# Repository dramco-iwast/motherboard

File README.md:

# motherboard
Design files (soft- and hardware) for the IWAST motherboard.

Needs reorganization.

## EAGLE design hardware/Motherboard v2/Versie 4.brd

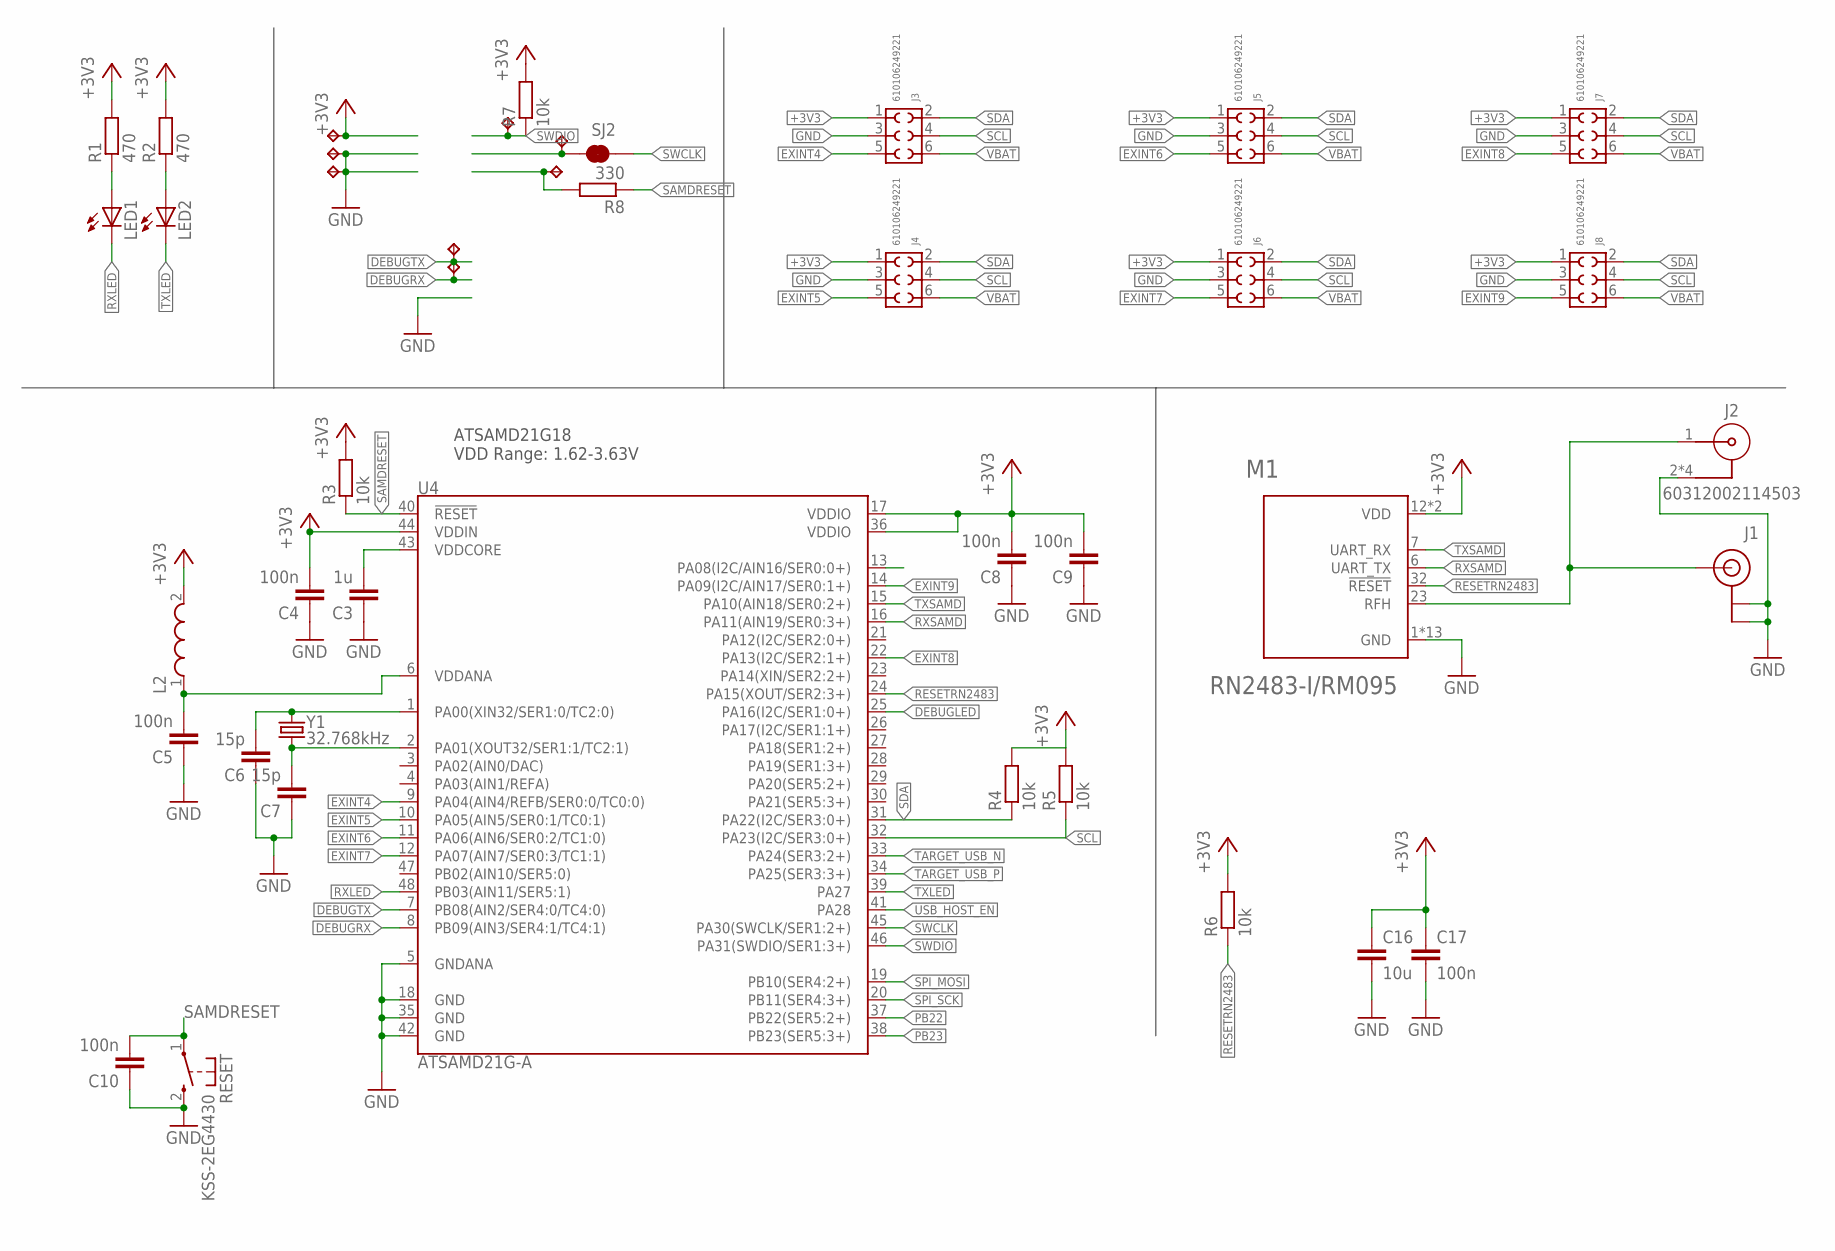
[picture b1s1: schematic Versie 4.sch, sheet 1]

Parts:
C3: 1u; C0603
C4, C5, C8, C9, C10, C17: 100n; C0603
C6, C7: 15p; C0603
C16: 10u; C0805
J1: U.FL
J2: 60312002114503
J3, J4, J5, J6, J7, J8: 610106249221
L2: WE-CBA_0603(WB/HS); WE-CBA_0603(W=2.2)
LED1, LED2: LEDCHIP-LED0603; CHIP-LED0603
M1: RN2483-I/RM095; MICROCHIP_RN2483-I/RM095
R1, R2: 470; R0603
R3, R4, R5, R6, R7: 10k; R0603
R8: 330; R0603
RESET: KSS-2EG4430
SJ2: JUMPER-PAD-2-NC_BY_TRACENO_SILK; PAD-JUMPER-2-NC_BY_TRACE_NO_SILK
TP1, TP2, TP3, TP4, TP5, TP6, TP7, TP8: TPB1,27; B1,27
U4: ATSAMD21G-A; TQFP-48
Y1: 32.768kHz; CRYSTAL-SMD-3.2X1.5MM

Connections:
+3V3: C4.2, C8.2, C9.2, C16.1, C17.1, J3.1, J4.1, J5.1, J6.1, J7.1, J8.1, L2.2, M1.12 (VDD), M1.34 (VDD), R1.2, R2.2, R3.2, R4.2, R5.2, R6.2, R7.2, TP1.TP, U4.17 (VDDIO), U4.36 (VDDIO), U4.44 (VDDIN); also elsewhere on the board
BUTTON: U4.13 (PA08(I2C/AIN16/SER0:0+)); also elsewhere on the board
DEBUGLED: U4.25 (PA16(I2C/SER1:0+)); also elsewhere on the board
DEBUGRX: TP8.TP, U4.8 (PB09(AIN3/SER4:1/TC4:1))
DEBUGTX: TP7.TP, U4.7 (PB08(AIN2/SER4:0/TC4:0))
EXINT4: J3.5, U4.9 (PA04(AIN4/REFB/SER0:0/TC0:0))
EXINT5: J4.5, U4.10 (PA05(AIN5/SER0:1/TC0:1))
EXINT6: J5.5, U4.11 (PA06(AIN6/SER0:2/TC1:0))
EXINT7: J6.5, U4.12 (PA07(AIN7/SER0:3/TC1:1))
EXINT8: J7.5, U4.22 (PA13(I2C/SER2:1+))
EXINT9: J8.5, U4.14 (PA09(I2C/AIN17/SER0:1+))
GND: C3.1, C4.1, C5.1, C6.1, C7.1, C8.1, C9.1, C10.1, C16.2, C17.2, J1.P$1 (GND), J1.P$2 (GND), J2.2, J2.3 (2), J2.4 (2), J2.5 (2), J3.3, J4.3, J5.3, J6.3, J7.3, J8.3, M1.1 (GND), M1.8 (GND), M1.11 (GND), M1.20 (GND), M1.21 (GND), M1.22 (GND), M1.24 (GND), M1.26 (GND), M1.27 (GND), M1.28 (GND), M1.33 (GND), M1.41 (GND), M1.47 (GND), RESET.2 (S), TP2.TP, TP3.TP, U4.5 (GNDANA), U4.18 (GND), U4.35 (GND), U4.42 (GND); also elsewhere on the board
unnamed: LED1.A, R1.1
unnamed: LED2.A, R2.1
unnamed: SJ2.2, TP5.TP
unnamed: C6.2, U4.1 (PA00(XIN32/SER1:0/TC2:0)), Y1.P$2 (2)
unnamed: C7.2, U4.2 (PA01(XOUT32/SER1:1/TC2:1)), Y1.P$1 (1)
unnamed: C5.2, L2.1, U4.6 (VDDANA)
unnamed: J1.P$3 (SIGNAL), J2.1, M1.23 (RFH)
unnamed: R8.2, TP6.TP
PB22: U4.37 (PB22(SER5:2+))
PB23: U4.38 (PB23(SER5:3+))
RESETRN2483: M1.32 (!RESET), R6.1, U4.24 (PA15(XOUT/SER2:3+))
RXLED: LED1.C, U4.48 (PB03(AIN11/SER5:1))
RXSAMD: M1.6 (UART_TX), U4.16 (PA11(AIN19/SER0:3+))
SAMDRESET: C10.2, R3.1, R8.1, RESET.1, U4.40 (!RESET!); also elsewhere on the board
SCL: J3.4, J4.4, J5.4, J6.4, J7.4, J8.4, R5.1, U4.32 (PA23(I2C/SER3:0+))
SDA: J3.2, J4.2, J5.2, J6.2, J7.2, J8.2, R4.1, U4.31 (PA22(I2C/SER3:0+))
SPI_MOSI: U4.19 (PB10(SER4:2+))
SPI_SCK: U4.20 (PB11(SER4:3+))
SWCLK: SJ2.1, U4.45 (PA30(SWCLK/SER1:2+))
SWDIO: R7.1, TP4.TP, U4.46 (PA31(SWDIO/SER1:3+))
TARGET_USB_N: U4.33 (PA24(SER3:2+)); also elsewhere on the board
TARGET_USB_P: U4.34 (PA25(SER3:3+)); also elsewhere on the board
TXLED: LED2.C, U4.39 (PA27)
TXSAMD: M1.7 (UART_RX), U4.15 (PA10(AIN18/SER0:2+))
USB_HOST_EN: U4.41 (PA28)
VBAT: J3.6, J4.6, J5.6, J6.6, J7.6, J8.6; also elsewhere on the board
VDDCORE: C3.2, U4.43 (VDDCORE)

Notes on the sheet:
ATSAMD21G18 VDD Range: 1.62-3.63V

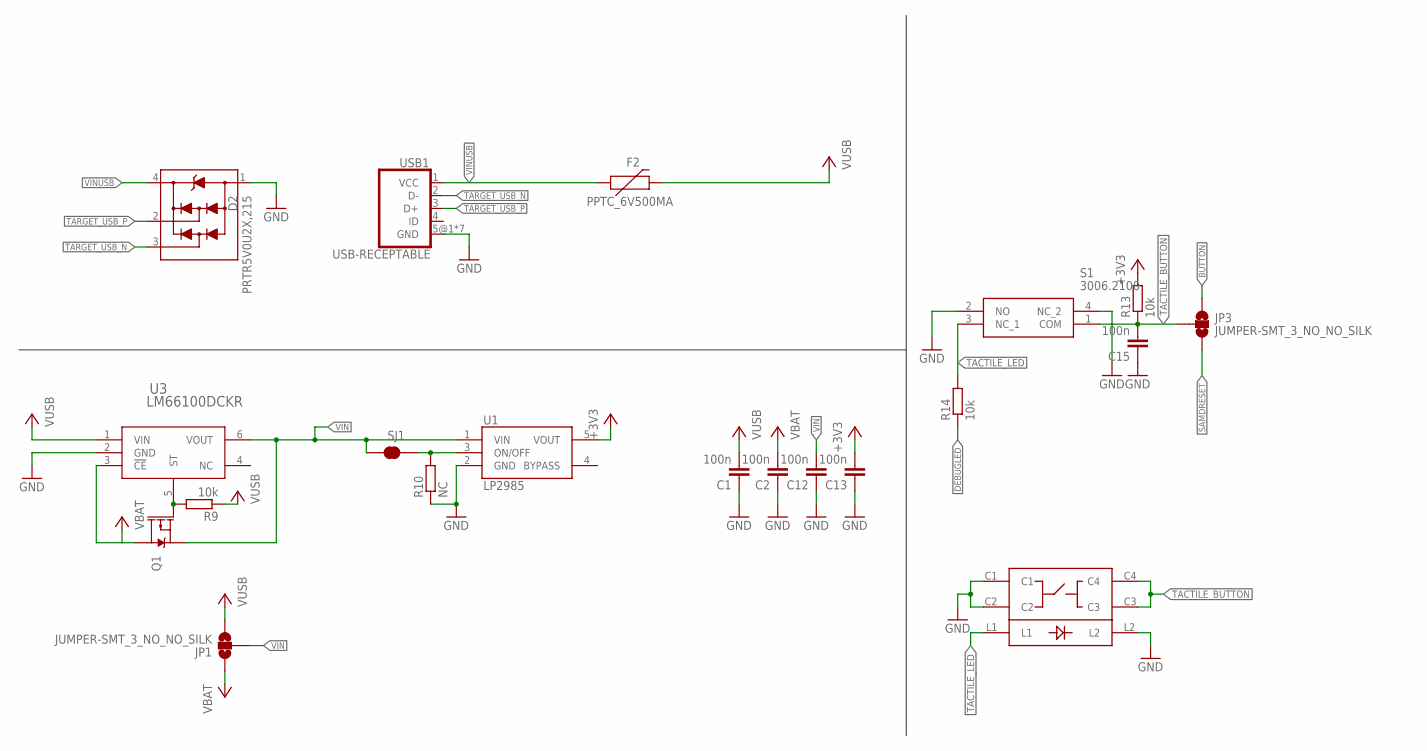
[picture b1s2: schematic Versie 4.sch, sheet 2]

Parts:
C1, C2, C12, C13, C15: 100n; C0603
D2: PRTR5V0U2X,215; SOT143B
F2: PPTC_6V500MA; 0805
JP1, JP3: JUMPER-SMT_3_NO_NO_SILK; SMT-JUMPER_3_0-NO_TRACE_NO-SILK
Q1: MOSFET_PCH-DMG2307L; SOT23-3
R9, R13, R14: 10k; R0603
R10: NC; R0603
S1: 3006.2100; 30062101
SJ1: JUMPER-PAD-2-NC_BY_TRACENO_SILK; PAD-JUMPER-2-NC_BY_TRACE_NO_SILK
U1: LP2985AIM5-3.3; SOT25
U3: LM66100DCKR; DCK6_TEX
U$1: LS1201
USB1: USB-RECEPTABLE; FCI-10103594-0001LF

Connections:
+3V3: C13.2, R13.2, U1.5 (VOUT); also elsewhere on the board
BUTTON: JP3.1; also elsewhere on the board
DEBUGLED: R14.1; also elsewhere on the board
GND: C1.1, C2.1, C12.1, C13.1, C15.1, D2.1, R10.1, S1.2 (NO), S1.4 (NC_2), U1.2 (GND), U3.2 (GND), U$1.C1, U$1.C2, U$1.L2, USB1.5@1 (GND), USB1.5@2 (GND), USB1.5@3 (GND), USB1.5@4 (GND), USB1.5@5 (GND), USB1.5@6 (GND), USB1.5@7 (GND); also elsewhere on the board
unnamed: Q1.1 (G), R9.2, U3.5 (ST)
ONOFF: R10.2, SJ1.1, U1.3 (ON/OFF)
SAMDRESET: JP3.3; also elsewhere on the board
TACTILE_BUTTON: C15.2, JP3.2, R13.1, S1.1 (COM), U$1.C3, U$1.C4
TACTILE_LED: R14.2, S1.3 (NC_1), U$1.L1
TARGET_USB_N: D2.3, USB1.2 (D-); also elsewhere on the board
TARGET_USB_P: D2.2, USB1.3 (D+); also elsewhere on the board
VBAT: C2.2, JP1.1, Q1.3 (D), U3.3 (!CE); also elsewhere on the board
VIN: C12.2, JP1.2, Q1.2 (S), SJ1.2, U1.1 (VIN), U3.6 (VOUT)
VINUSB: D2.4, F2.1, USB1.1 (VCC)
VUSB: C1.2, F2.2, JP1.3, R9.1, U3.1 (VIN)

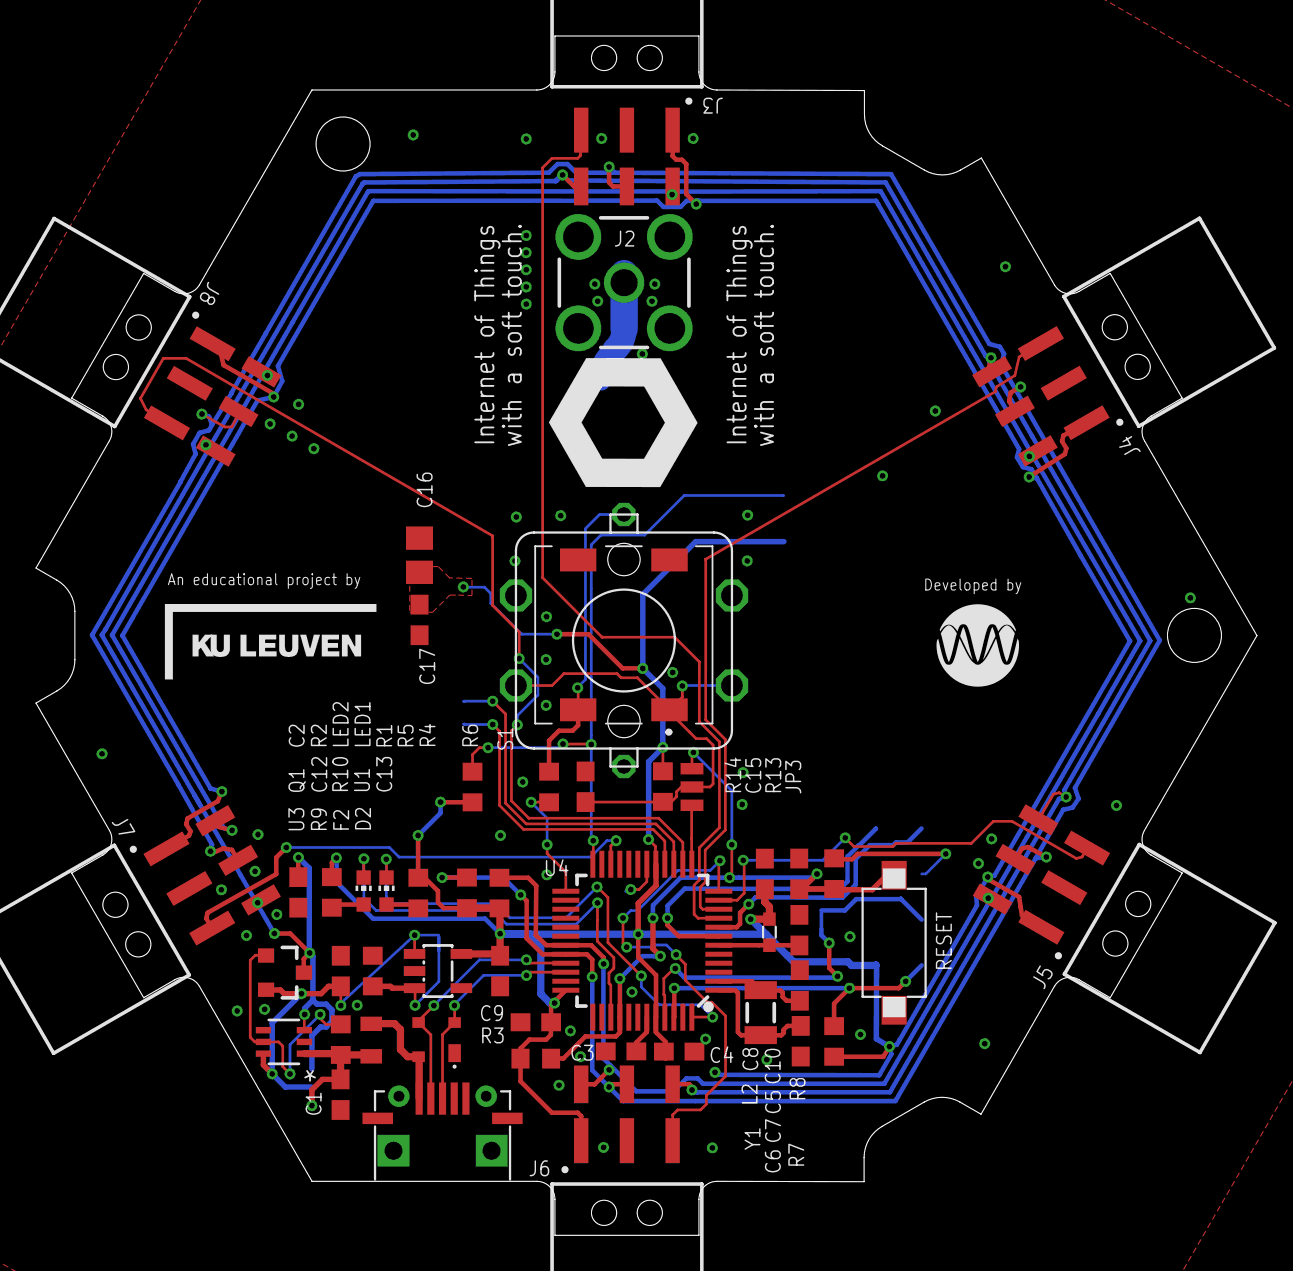
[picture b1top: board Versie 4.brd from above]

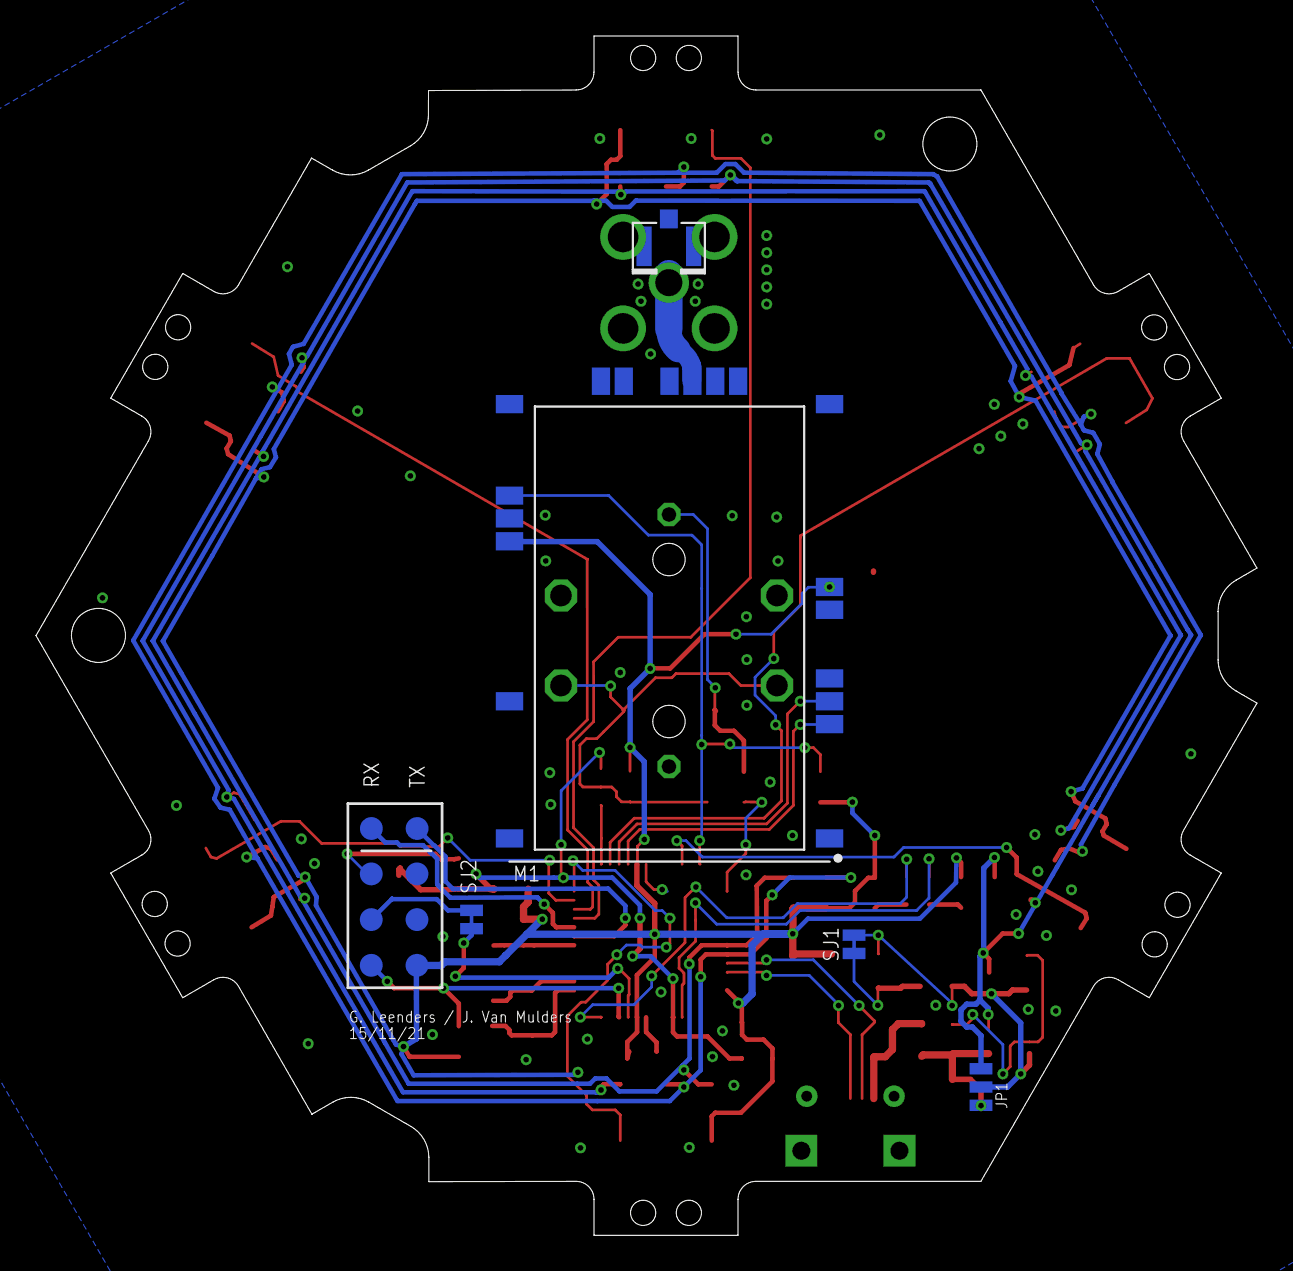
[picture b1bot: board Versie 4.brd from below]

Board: 2 copper layers, 67.8 x 66.6 mm, 62 parts (13 on the bottom side), 41 nets.

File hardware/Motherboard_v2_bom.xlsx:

Qty | Value | Device | Package | Parts | Description | Manufacturer Part Number (MPN) | Ordercode Farnell | Ordercode Mouser | Type
2 |  | JUMPER-PAD-2-NC_BY_TRACENO_SILK | PAD-JUMPER-2-NC_BY_TRACE_NO_SILK | SJ1, SJ2
1 |  | JUMPER-SMT_3_1-NC_TRACE_SILK | SMT-JUMPER_3_1-NC_TRACE_SILK | JP11 | Normally closed trace jumper (1 of 2 connections)
2 |  | LEDCHIP-LED0603 | CHIP-LED0603 | LED1, LED2 | LED | KP-2012QBC-D | 2217974 |  | Tape en reel, afgesneden
1 |  | MOSFET_PCH-DMG2307L | SOT23-3 | Q1 | P-channel MOSFETs | DMG2307L | 2061518 |  | Tape en reel, afgesneden
1 |  | PINHD-1X1 | 1X01 | JP2 | PIN HEADER
6 |  | PINHD-2X3 | 2X03 | JP3, JP4, JP5, JP6, JP7, JP8 | PIN HEADER | M20-7830346 | 7991983 |  | Per stuk
1 |  | WE-CBA_0603(WB/HS) | WE-CBA_0603(W=2.2) | L2 | WE-CBA SMD EMI Suppression Ferrite Bead | 782631331 | 3551389 |  | Tape en reel, afgesneden
11 | 100n | C-EUC0603 | C0603 | C1, C2, C3, C4, C5, C8, C9, C12, C13, C15, C17 | CAPACITOR, European symbol | C0603C104Z4VACTU | 2522395 |  | Tape en reel, afgesneden
9 | 10k | R-EU_R0603 | R0603 | R3, R4, R5, R6, R7, R9, R10, R13, R14 | RESISTOR, European symbol | MC0100W0603110K | 2845751 |  | Tape en reel, afgesneden
1 | 10u | C-EUC0805 | C0805 | C16 | CAPACITOR, European symbol | C0805C106Z8VACTU | 2725611 |  | Reel
2 | 15p | C-EUC0603 | C0603 | C6, C7 | CAPACITOR, European symbol | C0603C150K4GACTU | 2773124 |  | Tape en reel, afgesneden
1 | 30062100 | 30062100 | 30062101 | S1 | Tactile Switches TACTILE | 30062114 |  | 979-3006.2114 | Not specified
1 | 32.768kHz | CRYSTAL3.2X1.5MM | CRYSTAL-SMD-3.2X1.5MM | Y1 | Various standard crystals. Proven footprints. | ABS07-32.768KHZ-T | 2101347 |  | Tape en reel, afgesneden
1 | 330 | R-EU_R0603 | R0603 | R8 | RESISTOR, European symbol | MCWR06X3300FTL | 2447339 |  | Tape en reel, afgesneden
2 | 470 | R-EU_R0603 | R0603 | R1, R2 | RESISTOR, European symbol | RC0603JR-07470RL | 9233334 |  | Tape en reel, afgesneden
1 | ATSAMD21G-A | ATSAMD21G-A | TQFP-48 | U4 | Atmel SAMD21G SMART ARM-Based Microcontroller | ATSAMD21G18A-AUT | 2775015 |  | Per stuk
1 | KSS-2EG4430 | KSS-2EG4430 | KSS-2EG4430 | RESET | Size: 3x6mm | PTS636 SM43 SMTR LFS |  | 611-PTS636SM43SMTRLF | Reel / afgesneden
1 | LM66100DCKR | LM66100DCKR | DCK6_TEX | U3 |  | LM66100DCKR |  | 595-LM66100DCKR | Reel / afgesneden
1 | LP2985AIM5-3.3 | LP2985AIM5-3.3 | SOT25 | U1 | LP2985-N Micropower 150 mA Low-Noise Ultra Low-Dropout Regulator | LP2985AIM5-3.3/NOPB | 3122185 |  | Tape en reel, afgesneden
1 | PPTC_6V500MA | PPTC_6V500MA | 805 | F2 | Resettable Fuse PPTC | SMD0805B050TF | 3052501 |  | Tape en reel, afgesneden
1 | PRTR5V0U2X,215 | PRTR5V0U2X,215 | SOT143B | D2 | Ultra low capacitance double rail-to-rail ESD protection diode Check prices | PRTR5V0U2X,215 | 1524157 |  | Tape en reel, afgesneden
1 | RN2483 | RN2483 | RN2483 | U2 | RN2483 Microchip Low-Power Lora Transceiver Module | RN2483A-I/RM104 | 2920841 |  | Per stuk
8 | TPB1,27 | TPB1,27 | B1,27 | TP1, TP2, TP3, TP4, TP5, TP6, TP7, TP8 | Test pad
1 | U.FL | U.FL | U.FL | J1 | SMD antenna connector- WRL-09144 | U.FL-R-SMT-1(10) | 1688077 |  | Tape en reel, afgesneden
1 | USB-RECEPTABLE | USB-RECEPTABLE | FCI-10103594-0001LF | USB1 | USB Receptable | 10118194-0001LF | 2668482 |  | Tape en reel, afgesneden

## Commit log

2019-10-18 First upload
    Working test of AT command set and non-volatile storage of settings.
2019-10-24 Functionality update
    Added library for LoRaWAN connectivity
    Added Sensor class (not tested yet)
    Added NonVolatileConfig class (not tested yet)
2019-10-24 Removed obsolete files
2019-10-30 Small changes
2019-11-05 Support for polled sensing
    Partly tested (support for multiple metrics/sensor is still under development)
2019-11-07 Small changes
    Some small changes, mainly for testing
2019-11-14 Working NodeManager
    Added extra hardware serial for debugging (because Native USB looses connection in sleep).
    Nodemanager tested with 2 sensors (both polled and interrupt-based operation). Currently no multi-metric sensor support.
2019-11-14 Update main.cpp
    lora test application (working)
2019-11-18 restructured
2019-11-18 Low power testing
2019-11-19 intermediate push
2019-11-20 Temporary update
    Used new low power library.
    Changed file structure of LoRa library.
2019-11-27 Minor updates
    Minor update to NodeManager AT interface
    Temp update of LoraWAN en RN2483
2019-12-10 Modified hardware design of motherboard
2019-12-10 Low-power LoRa operation (modem sleep)
2020-01-15 Testing version
    This version can be used for system testing
2020-01-15 Testing with lora communication
2020-01-20 Bug fix in NodeManager
    Wrong callback for sixth interrupt pin
2020-01-21 LoRaWAN update
2020-01-21 Modified NodeManager loop behaviour.
    Also removed old files
2020-01-23 Modified NonVolatileConfig
2020-08-14 Increased IIC address scan range
2020-10-07 Updated NonVolatileConfig to include data accumulation setting
2020-10-08 Updated NodeManager and LoRaWAN
    Periodic wake-up every 60 seconds. Sleep can be interrupted without impacting the wake-up period.
    Added LED to LoRaWAN library
2020-10-08 Code version updates
2020-10-15 Update platformio.ini
    VERY_LOW_POWER build flag is essential for µA sleep currents
2020-10-15 ArduinoLowPower
    Added time-keeping to ArduinoLowPower
2020-10-15 NodeManager updated
    Improved sleep behavior. Started with support for data accumulation.
2020-10-21 Update ArduinoLowPower
    Sleep() can be used to sleep until previously set alarm
2020-10-21 Update DebugSerial.h
    Added include guards
    Added function to print byte buffer in hex format
2020-10-21 Update NodeManager
    Included status message support
    Updated sleep scheduling
2020-10-22 Update Sensor.cpp
    Clean-up.
2020-10-22 Update Sensor.h
    New define.
2020-10-22 Update platformio.ini
    Add ./src to the include path
2020-10-22 Update NodeManager.h
    New message format parameters.
2020-11-04 Updated NodeManager
    Status messages are sent immediately (even if data accumulation is enabled).
2020-11-04 Update NonVolatileConfig.cpp
    Fixed error with offset in non-volatile config
2020-11-04 Added option to disable status messages
2020-11-04 Added watchdog for stability
    Still in testing phase
2020-11-12 Watchdog reset is used to skip configuration phase
2020-11-12 Updated gitignore
2020-12-14 Motherboard v2
    Made by Guus
2021-01-26 Important updates
    Lora: SF11 = default DR, ADR enabled by default
    Nodemanager: extra wakeup safety added by use of watchdog
2021-01-27 ADR enabled
2021-02-04 NodeManager Update
    Non volatile configuration is only updated when motherboard is reconfigured (by AT commands)
2021-02-19 NodeManager updated
    System reset when connected sensors do not match with the stored configuration.
2021-05-18 Cleanup hardware
2021-06-03 Update LoRaWAN.cpp
    Updated LED control for the new motherboard hardware
2021-06-11 Added option to disable the use of confirmed messages
    Added option to disable the use of confirmed messages as this is not supported by all service providers. Also has an impact on ADR.
2021-09-03 Hardware v2
2021-09-17 Update lora led operation
2022-01-18 Custom ArduinoLowPower
2022-01-18 Updated NonVolatileConfig
    Support for storing Lora-related configuration
2022-01-18 Updated rn2xx3
    Small changes to support (customized) OTAA
2022-01-18 Updated NodeManager
    Supports new AT configuration commands to store and read lora-related settings
2022-01-26 Added hardware v4
2022-02-23 start led board v1
2022-02-23 boardled
2022-02-23 flash couple of times
2022-02-25 added iwast app eui
2022-02-25 moved default adr setting
2022-02-25 Update NodeManager.cpp
    derive board id from deviceEUI

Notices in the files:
parts and their libraries:
SparkFun-Fuses: Licensing: Creative Commons ShareAlike 4.0 International - https://creativecommons.org/licenses/by-sa/4.0
EagleLibrary_Wuerth_Elektronik_eiSos_rev: Copyright: Würth Elektronik
COPYRIGHT: Copyright (C) 2018 Accelerated Designs. All rights reserved
